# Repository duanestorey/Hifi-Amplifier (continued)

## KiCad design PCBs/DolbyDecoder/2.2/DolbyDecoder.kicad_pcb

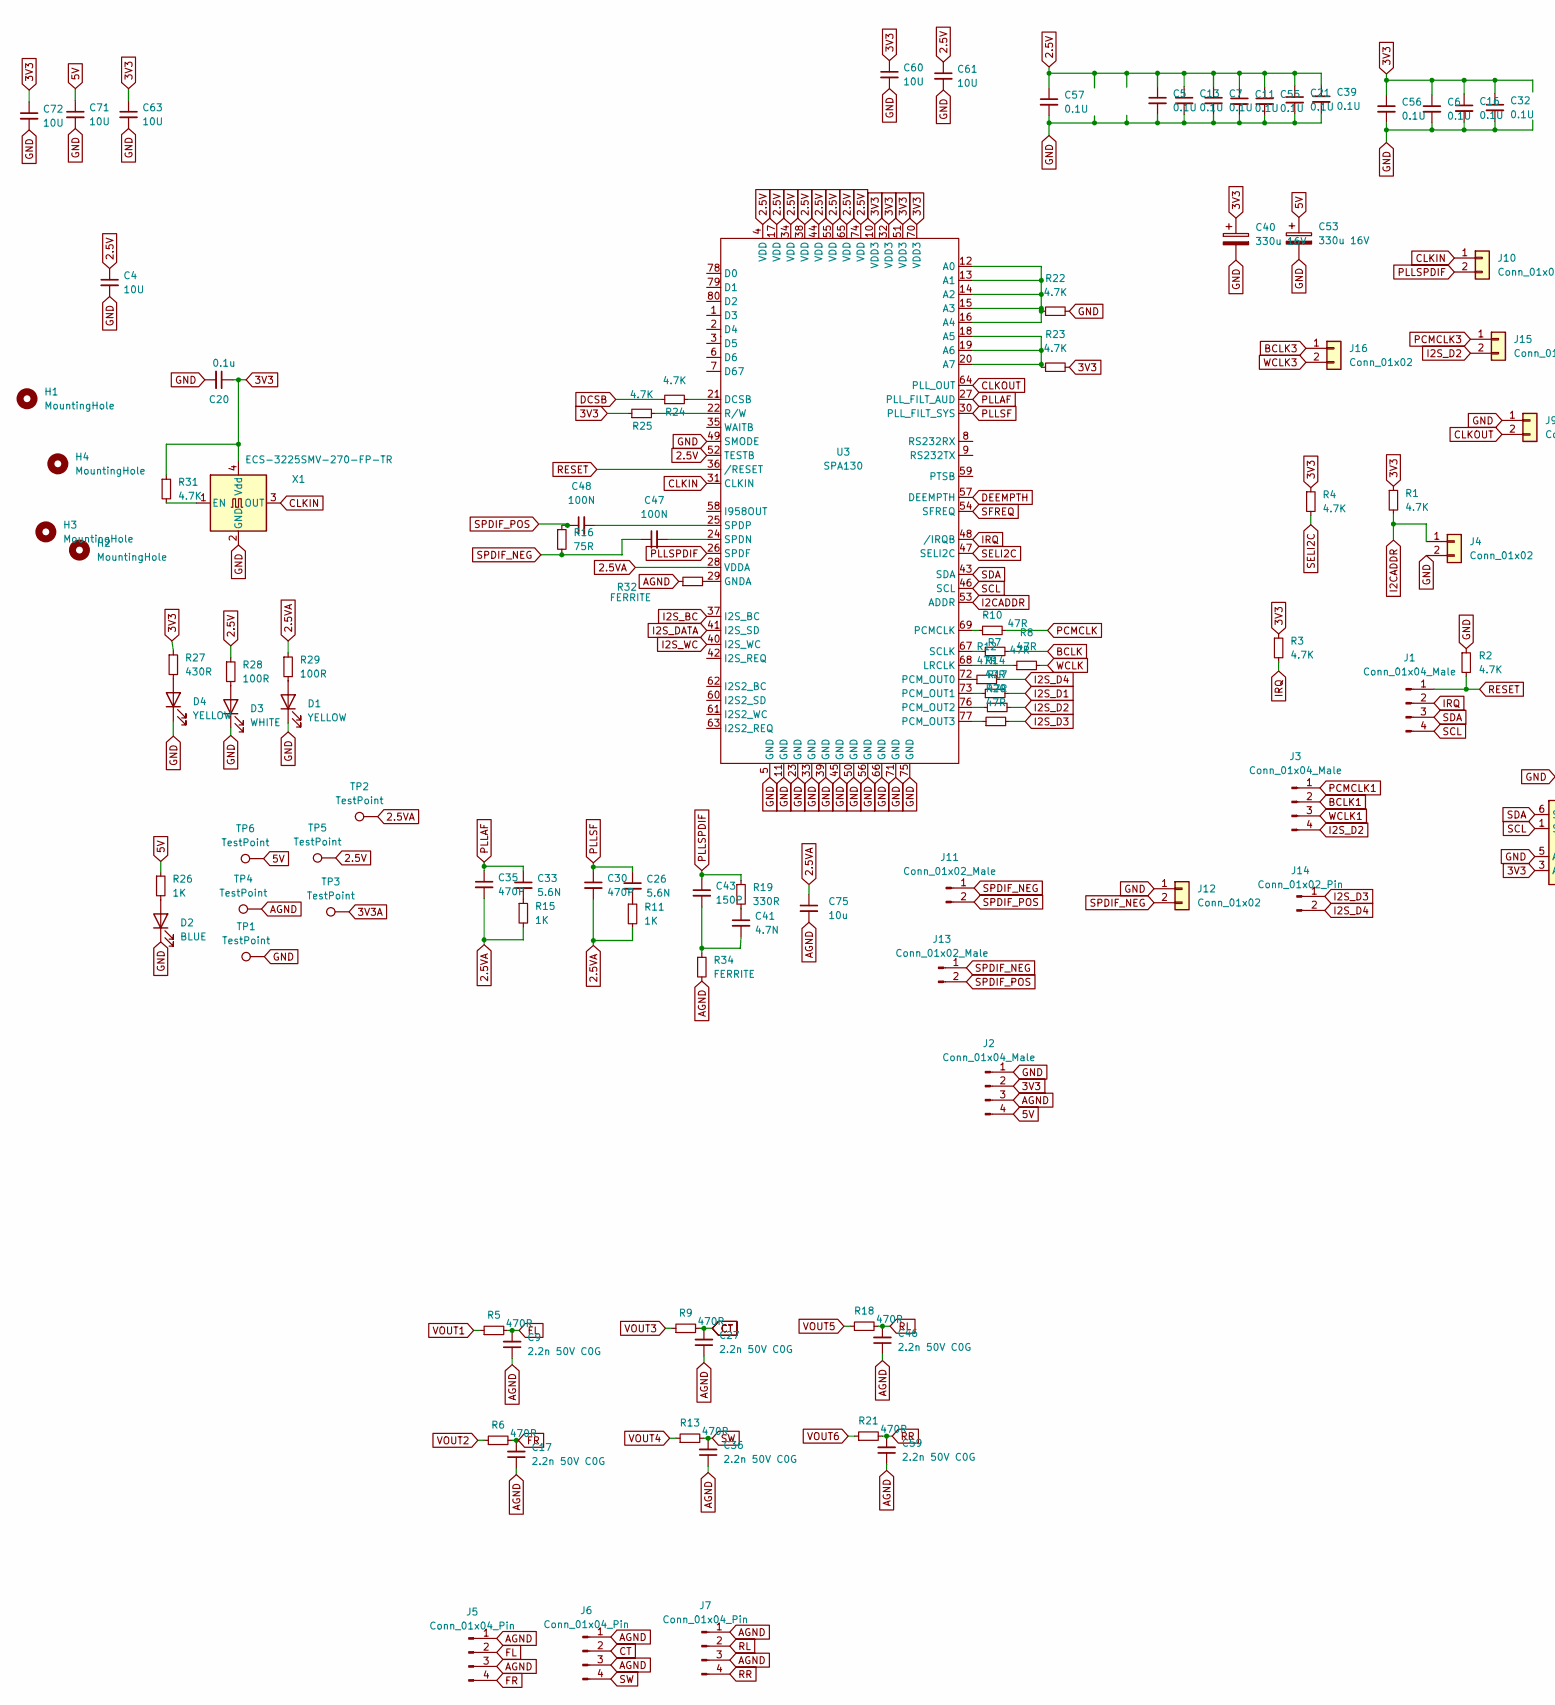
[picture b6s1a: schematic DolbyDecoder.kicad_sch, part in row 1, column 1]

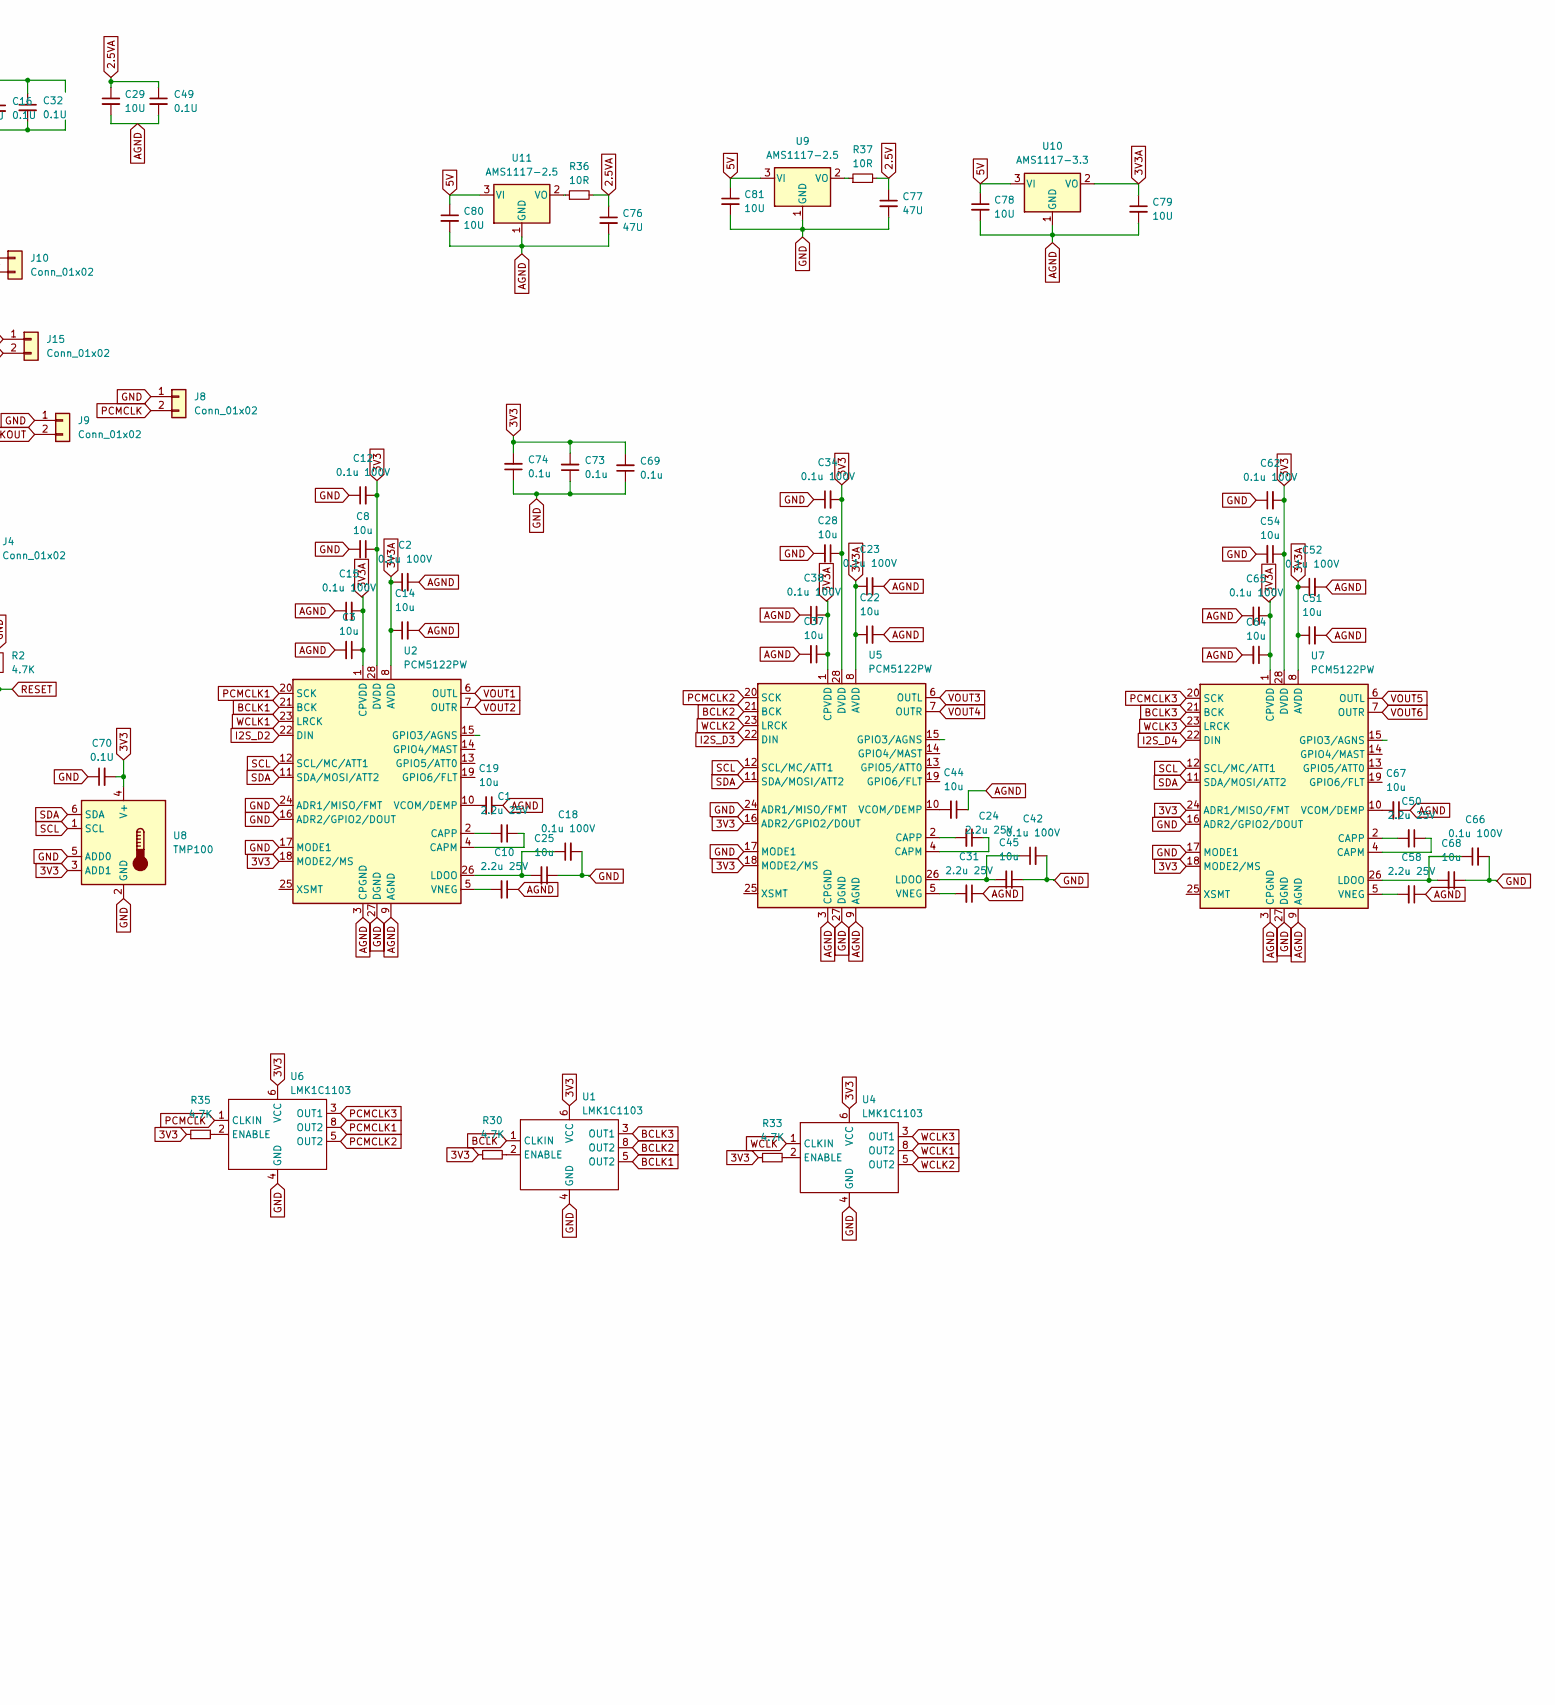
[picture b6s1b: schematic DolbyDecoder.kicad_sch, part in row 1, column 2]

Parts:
C1, C10, C24, C31, C50, C58: 2.2u 25V; C_1206_3216Metric_Pad1.33x1.80mm_HandSolder
C2, C12, C15, C18, C23, C34, C38, C42, C52, C62, C65, C66: 0.1u 100V; C_0805_2012Metric_Pad1.18x1.45mm_HandSolder
C3, C8, C14, C19, C22, C25, C28, C37, C44, C45, C51, C54, C64, C67, C68, C75: 10u; C_1206_3216Metric_Pad1.33x1.80mm_HandSolder
C4, C29, C60, C61, C63, C71, C72, C78, C79, C80, C81: 10U; C_1206_3216Metric_Pad1.33x1.80mm_HandSolder
C5, C6, C7, C11, C13, C16, C21, C32, C39, C49, C55, C56, C57, C70: 0.1U; C_0805_2012Metric_Pad1.18x1.45mm_HandSolder
C9, C17, C27, C36, C46, C59: 2.2n 50V C0G; C_1206_3216Metric_Pad1.33x1.80mm_HandSolder
C20, C69, C73, C74: 0.1u; C_0805_2012Metric_Pad1.18x1.45mm_HandSolder
C26, C33: 5.6N; C_0805_2012Metric_Pad1.18x1.45mm_HandSolder
C30, C35: 470P; C_0805_2012Metric_Pad1.18x1.45mm_HandSolder
C40, C53: 330u 16V; CP_Radial_D8.0mm_P2.50mm
C41: 4.7N; C_0805_2012Metric_Pad1.18x1.45mm_HandSolder
C43: 150P; C_0805_2012Metric_Pad1.18x1.45mm_HandSolder
C47, C48: 100N; C_0805_2012Metric_Pad1.18x1.45mm_HandSolder
C76, C77: 47U; C_1206_3216Metric_Pad1.33x1.80mm_HandSolder
D1, D4: YELLOW; LED_0805_2012Metric_Pad1.15x1.40mm_HandSolder
D2: BLUE; LED_0805_2012Metric_Pad1.15x1.40mm_HandSolder
D3: WHITE; LED_0805_2012Metric_Pad1.15x1.40mm_HandSolder
H1, H2, H3, H4: MountingHole; MountingHole_3.2mm_M3
J1: Conn_01x04_Male; JST_PH_B4B-PH-K_1x04_P2.00mm_Vertical
J2: Conn_01x04_Male; JST_XH_B4B-XH-A_1x04_P2.50mm_Vertical
J3: Conn_01x04_Male; PinHeader_1x04_P2.54mm_Vertical
J4, J8, J9, J10, J12, J15, J16: Conn_01x02; PinHeader_1x02_P2.54mm_Vertical
J5, J6, J7: Conn_01x04_Pin; JST_PH_B4B-PH-K_1x04_P2.00mm_Vertical
J11: Conn_01x02_Male; JST_XH_B2B-XH-A_1x02_P2.50mm_Vertical
J13: Conn_01x02_Male; PinHeader_1x02_P2.54mm_Vertical
J14: Conn_01x02_Pin; PinHeader_1x02_P2.54mm_Vertical
R1, R2, R3, R4, R22, R23, R24, R25, R30, R31, R33, R35: 4.7K; R_0603_1608Metric_Pad0.98x0.95mm_HandSolder
R5, R6, R9, R13, R18, R21: 470R; R_1206_3216Metric_Pad1.30x1.75mm_HandSolder
R7, R8, R10, R12, R14, R17, R20: 47R; R_0805_2012Metric_Pad1.20x1.40mm_HandSolder
R11, R15, R26: 1K; R_0603_1608Metric_Pad0.98x0.95mm_HandSolder
R16: 75R; R_0603_1608Metric_Pad0.98x0.95mm_HandSolder
R19: 330R; R_0603_1608Metric_Pad0.98x0.95mm_HandSolder
R27: 430R; R_0603_1608Metric_Pad0.98x0.95mm_HandSolder
R28, R29: 100R; R_0603_1608Metric_Pad0.98x0.95mm_HandSolder
R32, R34: FERRITE; R_0603_1608Metric_Pad0.98x0.95mm_HandSolder
R36, R37: 10R; R_0603_1608Metric_Pad0.98x0.95mm_HandSolder
TP1, TP2, TP3, TP4, TP5, TP6: TestPoint; TestPoint_THTPad_1.5x1.5mm_Drill0.7mm
U1, U4, U6: LMK1C1103; TSSOP-8_4.4x3mm_P0.65mm
U2, U5, U7: PCM5122PW; TSSOP-28_4.4x9.7mm_P0.65mm
U3: SPA130; LQFP-80_14x14mm_P0.65mm
U8: TMP100; SOT-23-6
U9, U11: AMS1117-2.5; SOT-223
U10: AMS1117-3.3; SOT-223
X1: ECS-3225SMV-270-FP-TR; Oscillator_SMD_EuroQuartz_XO32-4Pin_3.2x2.5mm_HandSoldering

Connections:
2.5V: C4.1, C5.1, C7.1, C11.1, C13.1, C21.1, C39.1, C55.1, C57.1, C61.1, C77.1, R28.1, R37.2, TP5.1, U3.4 (VDD), U3.17 (VDD), U3.34 (VDD), U3.38 (VDD), U3.44 (VDD), U3.52 (TESTB), U3.55 (VDD), U3.65 (VDD), U3.74 (VDD)
2.5VA: C29.1, C30.2, C35.2, C49.1, C75.1, C76.1, R11.2, R15.2, R29.1, R36.2, TP2.1, U3.28 (VDDA)
3V3: C6.1, C8.1, C12.2, C16.1, C20.1, C28.1, C32.1, C34.2, C40.1, C54.1, C56.1, C60.1, C62.2, C63.1, C69.2, C70.2, C72.1, C73.2, C74.2, J2.2, R1.1, R3.1, R4.1, R23.2, R25.1, R27.1, R30.1, R31.1, R33.1, R35.1, U1.6 (VCC), U2.18 (MODE2/MS), U2.28 (DVDD), U3.10 (VDD3), U3.32 (VDD3), U3.51 (VDD3), U3.70 (VDD3), U4.6 (VCC), U5.16 (ADR2/GPIO2/DOUT), U5.18 (MODE2/MS), U5.28 (DVDD), U6.6 (VCC), U7.18 (MODE2/MS), U7.24 (ADR1/MISO/FMT), U7.28 (DVDD), U8.3 (ADD1), U8.4 (V+), X1.4 (Vdd)
3V3A: C2.1, C3.1, C14.1, C15.2, C22.1, C23.1, C37.1, C38.2, C51.1, C52.1, C64.1, C65.2, C79.1, TP3.1, U2.1 (CPVDD), U2.8 (AVDD), U5.1 (CPVDD), U5.8 (AVDD), U7.1 (CPVDD), U7.8 (AVDD), U10.2 (VO)
5V: C53.1, C71.1, C78.1, C80.1, C81.1, J2.4, R26.1, TP6.1, U9.3 (VI), U10.3 (VI), U11.3 (VI)
AGND: C2.2, C3.2, C9.1, C10.1, C14.2, C15.1, C17.1, C19.1, C22.2, C23.2, C27.1, C29.2, C31.1, C36.1, C37.2, C38.1, C44.1, C46.1, C49.2, C51.2, C52.2, C58.1, C59.1, C64.2, C65.1, C67.1, C75.2, C76.2, C78.2, C79.2, C80.2, J2.3, J5.1, J5.3, J6.1, J6.3, J7.1, J7.3, R32.1, R34.2, TP4.1, U2.3 (CPGND), U2.9 (AGND), U5.3 (CPGND), U5.9 (AGND), U7.3 (CPGND), U7.9 (AGND), U10.1 (GND), U11.1 (GND)
BCLK: R7.2, U1.1 (CLKIN)
BCLK1: J3.2, U1.5 (OUT2), U2.21 (BCK)
BCLK2: U1.8 (OUT2), U5.21 (BCK)
BCLK3: J16.1, U1.3 (OUT1), U7.21 (BCK)
CLKIN: J10.1, U3.31 (CLKIN), X1.3 (OUT)
CLKOUT: J9.2, U3.64 (PLL_OUT)
CT: C27.2, J6.2, R9.2
DCSB: R24.1
DEEMPTH: U3.57 (DEEMPTH)
FL: C9.2, J5.2, R5.2
FR: C17.2, J5.4, R6.2
GND: C4.2, C5.2, C6.2, C7.2, C8.2, C11.2, C12.1, C13.2, C16.2, C18.2, C20.2, C21.2, C25.1, C28.2, C32.2, C34.1, C39.2, C40.2, C42.2, C45.1, C53.2, C54.2, C55.2, C56.2, C57.2, C60.2, C61.2, C62.1, C63.2, C66.2, C68.1, C69.1, C70.1, C71.2, C72.2, C73.1, C74.1, C77.2, C81.2, D1.1 (K), D2.1 (K), D3.1 (K), D4.1 (K), J2.1, J4.2, J8.1, J9.1, J12.1, R2.1, R22.2, TP1.1, U1.4 (GND), U2.16 (ADR2/GPIO2/DOUT), U2.17 (MODE1), U2.24 (ADR1/MISO/FMT), U2.27 (DGND), U3.5 (GND), U3.11 (GND), U3.23 (GND), U3.33 (GND), U3.39 (GND), U3.45 (GND), U3.49 (SMODE), U3.50 (GND), U3.56 (GND), U3.66 (GND), U3.71 (GND), U3.75 (GND), U4.4 (GND), U5.17 (MODE1), U5.24 (ADR1/MISO/FMT), U5.27 (DGND), U6.4 (GND), U7.16 (ADR2/GPIO2/DOUT), U7.17 (MODE1), U7.27 (DGND), U8.2 (GND), U8.5 (ADD0), U9.1 (GND), X1.2 (GND)
I2CADDR: J4.1, R1.2, U3.53 (ADDR)
I2S_BC: U3.37 (I2S_BC)
I2S_D1: R14.2
I2S_D2: J3.4, J15.2, R17.2, U2.22 (DIN)
I2S_D3: J14.1, R20.2, U5.22 (DIN)
I2S_D4: J14.2, R12.2, U7.22 (DIN)
I2S_DATA: U3.41 (I2S_SD)
I2S_WC: U3.40 (I2S_WC)
IRQ: J1.2, R3.2, U3.48 (/IRQB)
unnamed: C26.2, R11.1
unnamed: C33.2, R15.1
unnamed: C41.1, R19.2
unnamed: C41.2, C43.2, R34.1
unnamed: D1.2 (A), R29.2
unnamed: D2.2 (A), R26.2
unnamed: D3.2 (A), R28.2
unnamed: D4.2 (A), R27.2
unnamed: R30.2, U1.2 (ENABLE)
unnamed: C1.1, U2.4 (CAPM)
unnamed: C1.2, U2.2 (CAPP)
unnamed: C18.1, C25.2, U2.26 (LDOO)
unnamed: C19.2, U2.10 (VCOM/DEMP)
unnamed: C10.2, U2.5 (VNEG)
unnamed: R22.1, U3.12 (A0), U3.13 (A1), U3.14 (A2), U3.15 (A3), U3.16 (A4)
unnamed: R23.1, U3.18 (A5), U3.19 (A6), U3.20 (A7)
unnamed: R24.2, U3.21 (DCSB)
unnamed: R32.2, U3.29 (GNDA)
unnamed: R8.1, U3.68 (LRCLK)
unnamed: R10.1, U3.69 (PCMCLK)
unnamed: R12.1, U3.72 (PCM_OUT0)
unnamed: R14.1, U3.73 (PCM_OUT1)
unnamed: R17.1, U3.76 (PCM_OUT2)
unnamed: R20.1, U3.77 (PCM_OUT3)
unnamed: R25.2, U3.22 (R/W)
unnamed: R7.1, U3.67 (SCLK)
unnamed: C47.2, U3.24 (SPDN)
unnamed: C48.2, U3.25 (SPDP)
unnamed: R33.2, U4.2 (ENABLE)
unnamed: C24.1, U5.4 (CAPM)
unnamed: C24.2, U5.2 (CAPP)
unnamed: C42.1, C45.2, U5.26 (LDOO)
unnamed: C44.2, U5.10 (VCOM/DEMP)
unnamed: C31.2, U5.5 (VNEG)
unnamed: R35.2, U6.2 (ENABLE)
unnamed: C50.1, U7.4 (CAPM)
unnamed: C50.2, U7.2 (CAPP)
unnamed: C66.1, C68.2, U7.26 (LDOO)
unnamed: C67.2, U7.10 (VCOM/DEMP)
unnamed: C58.2, U7.5 (VNEG)
unnamed: R37.1, U9.2 (VO)
unnamed: R36.1, U11.2 (VO)
unnamed: R31.2, X1.1 (EN)
PCMCLK: J8.2, R10.2, U6.1 (CLKIN)
PCMCLK1: J3.1, U2.20 (SCK), U6.8 (OUT2)
PCMCLK2: U5.20 (SCK), U6.5 (OUT2)
PCMCLK3: J15.1, U6.3 (OUT1), U7.20 (SCK)
PLLAF: C33.1, C35.1, U3.27 (PLL_FILT_AUD)
PLLSF: C26.1, C30.1, U3.30 (PLL_FILT_SYS)
PLLSPDIF: C43.1, J10.2, R19.1, U3.26 (SPDF)
RESET: J1.1, R2.2, U3.36 (/RESET)
RL: C46.2, J7.2, R18.2
RR: C59.2, J7.4, R21.2
SCL: J1.4, U2.12 (SCL/MC/ATT1), U3.46 (SCL), U5.12 (SCL/MC/ATT1), U7.12 (SCL/MC/ATT1), U8.1 (SCL)
SDA: J1.3, U2.11 (SDA/MOSI/ATT2), U3.43 (SDA), U5.11 (SDA/MOSI/ATT2), U7.11 (SDA/MOSI/ATT2), U8.6 (SDA)
SELI2C: R4.2, U3.47 (SELI2C)
SFREQ: U3.54 (SFREQ)
SPDIF_NEG: C47.1, J11.1, J12.2, J13.1, R16.2
SPDIF_POS: C48.1, J11.2, J13.2, R16.1
SW: C36.2, J6.4, R13.2
VOUT1: R5.1, U2.6 (OUTL)
VOUT2: R6.1, U2.7 (OUTR)
VOUT3: R9.1, U5.6 (OUTL)
VOUT4: R13.1, U5.7 (OUTR)
VOUT5: R18.1, U7.6 (OUTL)
VOUT6: R21.1, U7.7 (OUTR)
WCLK: R8.2, U4.1 (CLKIN)
WCLK1: J3.3, U2.23 (LRCK), U4.8 (OUT2)
WCLK2: U4.5 (OUT2), U5.23 (LRCK)
WCLK3: J16.2, U4.3 (OUT1), U7.23 (LRCK)

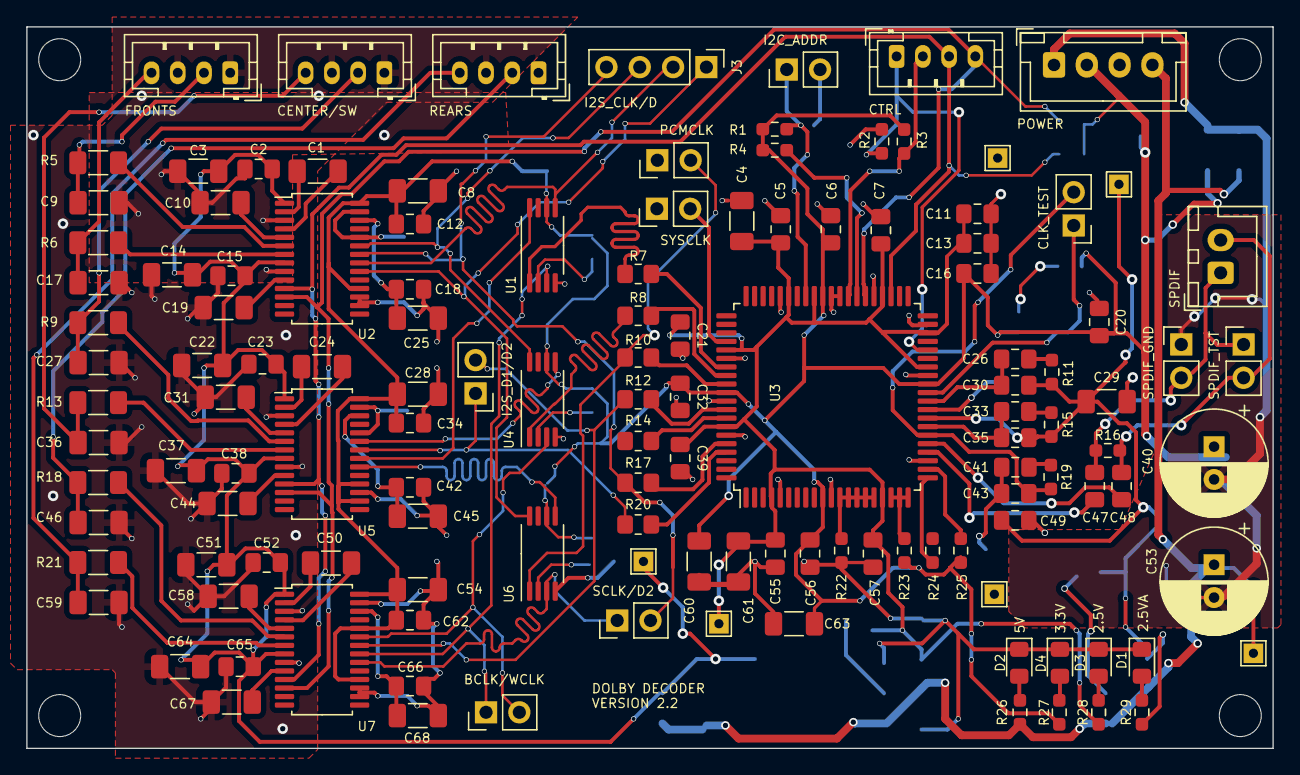
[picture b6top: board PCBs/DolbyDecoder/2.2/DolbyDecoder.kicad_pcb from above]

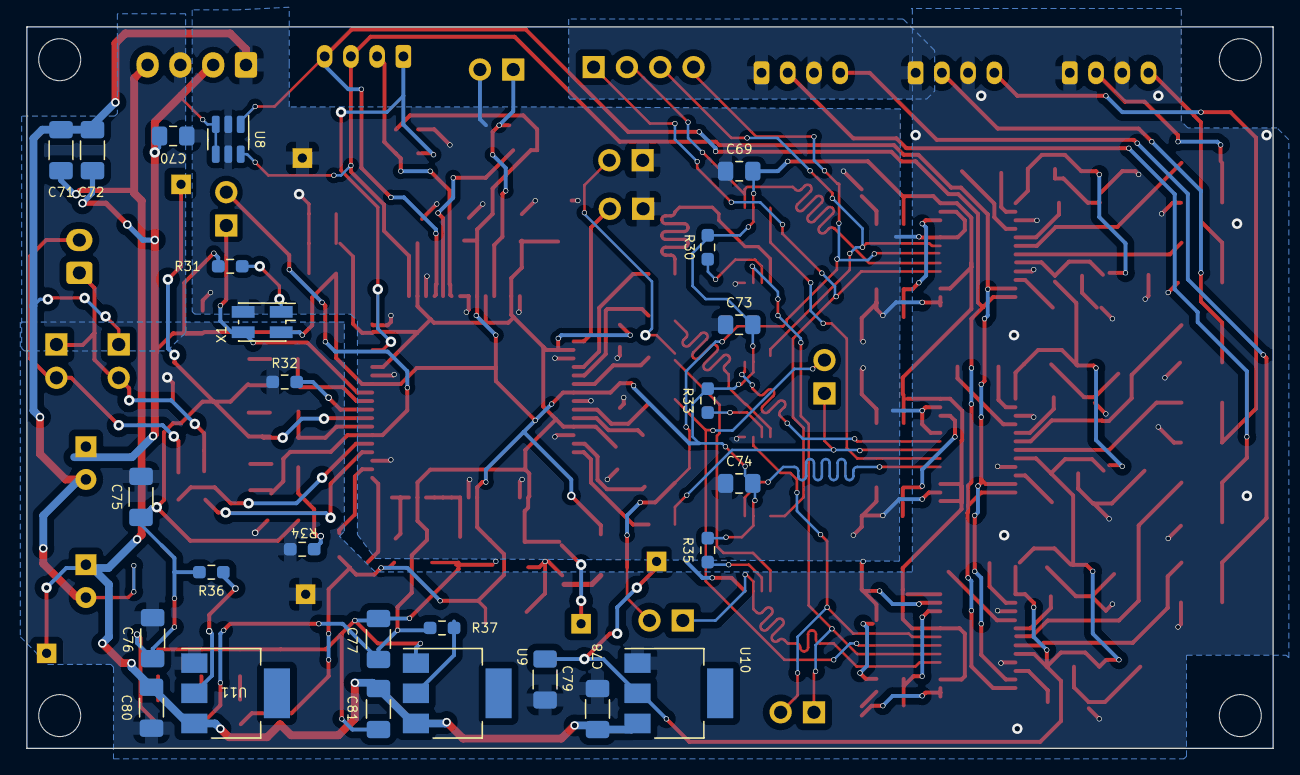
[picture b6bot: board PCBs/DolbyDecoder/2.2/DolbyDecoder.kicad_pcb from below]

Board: 2 copper layers, 95.0 x 55.0 mm, 160 parts (26 on the bottom side), 90 nets.
